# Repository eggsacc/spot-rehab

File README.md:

<div align="center">

# 🐾 Spot Rehabilitation

**Diagnosing & repairing a Boston Dynamics _Spot_ quadruped robot**

NUS · Undergraduate Research Opportunities Programme (UROP)

</div>

> [!NOTE]
> **🏁 This project wrapped up on 27 July 2026.**

## 📖 About

Years of neglect left Spot in a pitiful state: dead batteries and a broken leg. Instead of surrendering him to the shelter, we volunteered to bring him back and give him the love every dog deserves ❤️🦴. This repository documents the diagnostics and repair process of this big yellow dog.

## 🐶 Dog Status
>✅ Fully operational!

<div align="center">
  
</div>

---

## 👀 Overview

| | 🩻 On arrival | 🏁 At close |
|---|---|---|
| **Power** | Both battery modules refused to charge | Both packs rebuilt on their OEM BMS, full charge verified |
| **Mobility** | Left hind hip-X fails to move | Walks forward & backward, climbs stairs |
| **Perception** | Rear depth camera bricked (StereoProto fault) | Firmware transplanted from side camera, camera successfully inits |
| **Autonomy** | — | Autowalk missions + SDK mission behaviour trees |

## 📊 Subsystem Status

| Subsystem | Flag | Notes |
|-----------|----|-------|
| 🔋 **Power & Battery** | ✅ Complete | Pack #1, #2 rebuilt & verified (full charge, firmware updated) |
| 🦿 **Actuators & Legs** | ✅ Complete | Output stage encoder repaired |
| 🧠 **Compute & Mainboard** | ✅ Complete | Successful AutoWalk missions |
| 📷 **Sensors & Cameras** | ✅ Complete | Rear RealSense camera firmware fixed |
| 🦴 **Chassis & Mechanical** | ✅ Complete | Fully reassembled with new screws + threadlock |

---

## 🚶 AutoWalk

Multiple AutoWalk missions were performed to test Spot's capabilities. Below is an example mission using Spot to map out 3 levels of a building. The global map is reconstructed by transforming each waypoint snapshot's sensor payload into the common seed frame using the anchoring solution stored in the graph.

Recorded missions can be found in [/spot-autowalk-collections](./spot-autowalk-collections/).

>**Top-down view.** White circles represent waypoints recorded by Spot; blue lines are the connecting edges.

>**Side view.** 3 stories and staircases visible.

>**3D point cloud render** using [CloudCompare viewer](https://www.cloudcompare.org/).

🔍 [Autowalk decode deep dive](data/software/spot-autowalk-deep-dive.md) · 🌲 [Custom mission behaviour tree](data/software/autowalk-mission-behaviour-tree.md) · 🐍 [Scripts](spot-autowalk-collections/)

---

## 🗒️ Repair Log

Every session is written up as a dated log, grouped by subsystem:
[`docs/battery/`](docs/battery/) · [`docs/motor/`](docs/motor/) · [`docs/software/`](docs/software/)

> [!TIP]
> 📄 **Final UROP report:** [`report/urop-report.md`](report/urop-report.md)
> 📄 **Consolidated subsystem report:** [Battery pack repair](docs/subsystems/battery/battery-repair.md)

---

## 🔭 Future Work

Spot is fully usable as it stands, but is showing signs of component degradation.

>**Issue:** Spot check warns that the right hind hip-X encoder is <20% health. Testing has confirmed the issue to be the degraded ferrite Nonius magnetic ring that is tracked by the output stage encoder.

>**Recommended fix:** Purchase new Nonius ring from [Hutchinson](https://precisionsealingsystems.hutchinson.com/wp-content/uploads/2023/11/NoniusRing_datasheet.pdf), which was researched to match the dimensions of the OEM encoder ring. Opt for the rubber version for longer operation life.

---

## 🗂️ Repository Layout

```
spot-rehab/
├── README.md                   ← Project overview & status board (this file)
├── report/                     ← Final UROP report (Markdown, DOCX & build script)
├── templates/
│   └── dev-log-template.md     ← Copy this to start a new session log
├── data/                       ← Knowledge & reference pages
│   ├── electrical/             ← Encoder PCB, EEPROM, connector reference
│   └── software/               ← SDK, GraphNav/Autowalk, spot_ros2, setup guide, lit review
├── spot-autowalk-collections/  ← Recorded missions, decode & behaviour-tree scripts
└── docs/
    ├── assets/                 ← Shared images & media, referenced by all docs
    ├── battery/                ← Battery repair session logs
    ├── motor/                  ← Motor / actuator / encoder session logs
    ├── software/               ← Software / autonomy / SDK session logs
    └── subsystems/             ← Consolidated per-subsystem reports
        └── battery/battery-repair.md
```

## 🔗 Extras

[`spot_diagnostics`](https://github.com/Kmyming/spot_diagnostics) — our ROS 2 joint-feedback diagnostics node + web dashboard (see [software log](docs/software/2026-06-10-diagnostics-script.md))

## 👥 Team

| Name | Role |
|------|------|
| [@eggsacc](https://github.com/eggsacc) | UROP Researcher |
| [@Kmyming](https://github.com/Kmyming) | UROP Researcher |
| [@NickInSynchronicity](https://github.com/NickInSynchronicity) | Project Supervisor |

---

<div align="center">

**🐾 Spot is a good boi again 🦴**

<sub>Last updated: 2026-07-27 · Project concluded</sub>

</div>

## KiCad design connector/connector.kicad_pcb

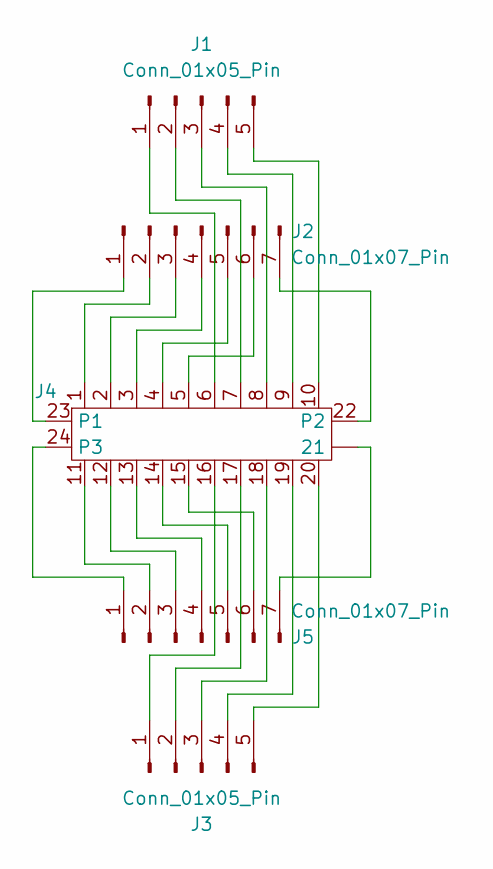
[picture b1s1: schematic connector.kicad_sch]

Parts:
J1, J3: Conn_01x05_Pin; PinHeader_1x05_P2.54mm_Vertical
J2, J5: Conn_01x07_Pin; PinHeader_1x07_P2.54mm_Vertical
J4: FX23-20P-0.5SVxx

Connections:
unnamed: J1.1, J4.6
unnamed: J1.2, J4.7
unnamed: J1.3, J4.8
unnamed: J1.4, J4.9
unnamed: J1.5, J4.10
unnamed: J2.1, J4.23 (P1)
unnamed: J2.2, J4.1
unnamed: J2.3, J4.2
unnamed: J2.4, J4.3
unnamed: J2.5, J4.4
unnamed: J2.6, J4.5
unnamed: J2.7, J4.22 (P2)
unnamed: J3.1, J4.16
unnamed: J3.2, J4.17
unnamed: J3.3, J4.18
unnamed: J3.4, J4.19
unnamed: J3.5, J4.20
unnamed: J4. (21), J5.7
unnamed: J4.24 (P3), J5.1
unnamed: J4.11, J5.2
unnamed: J4.12, J5.3
unnamed: J4.13, J5.4
unnamed: J4.14, J5.5
unnamed: J4.15, J5.6

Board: 2 copper layers, 5 parts (0 on the bottom side), 23 nets, no tracks yet.

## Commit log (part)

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2026-05-28 yz commit
2026-05-28 change filetype .txt->.md
2026-05-28 docs(logs): ros2 jazzy setup & battery assembly update
2026-06-02 docs: 2026-05-29 repair log update
2026-06-04 docs: 2026-06-02 battery assembly update
2026-06-07 change devlog name
2026-06-11 2026-06-11 docs update
2026-06-18 docs(repair-log): add driver diagnostics log
2026-06-18 readme: update battery repair status
2026-06-19 19-06-2026: docs update
2026-06-19 docs(repair-log): added images
2026-06-25 docs(repair-log): updated missing logs
2026-06-29 docs update: 2026-06-19 media addition
2026-06-30 docs(repair-log): encoder swap log
2026-06-30 docs(repair-log): updated 06-30 log
